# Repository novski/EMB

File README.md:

# EMB

Embedded-Rack is a multi SoC Powersupply with i2c connections.
It can be used to power up to 13 Raspberry Pi's and
 one Microcontroller to monitor Powerconsumption in Rackcase.

## How to

- Get a 19 inch DIN Rack similar to this from [schroff](https://schroff.nvent.com/products/19-subracks).

- Create a Backcover like in the drawing of /powersupply 
accordingly to your powersupply. I use this [MeanWell RSP-200-5](https://www.meanwell.com/productPdf.aspx?i=437)

- Connect a Poweroutlet (with fuse) and solder it to the 
psu and the psu to the backplane with carefully chosen cable 
diameter regarding your psu. 

- Get some Backplane connectors with 24x2.54mm pinn's 
like this from [aliex](https://de.aliexpress.com/wholesale?catId=0&initiative_id=SB_20220409111809&SearchText=pcb+edge+connector).

- Solder some connectors to a daughter-card and push your SoC 
on it.
pi: [mouser](http://ch.mouser.com/Search/ProductDetail.aspx?R=M20-6102045virtualkey57420000virtualkey855-M20-6102045)

- Stick the daughter-board in to the backplane.

## Powermeasureing

The i2c connection between all SoC's can be used as plane 
communication while adding an TI INA219 can be interessting 
to measure power over a board separate. Check the adafruit 
repo's for software and the schematic for parts.

## Impressions

## Disclaimer

All granted for free as in speech, without waranty.
(means that you can use, modify, share, sell if you like. 
But don't try to sue me for mistakes you do yourself.)
Be carefull with Power and re-calculate all wires according 
to your needs.

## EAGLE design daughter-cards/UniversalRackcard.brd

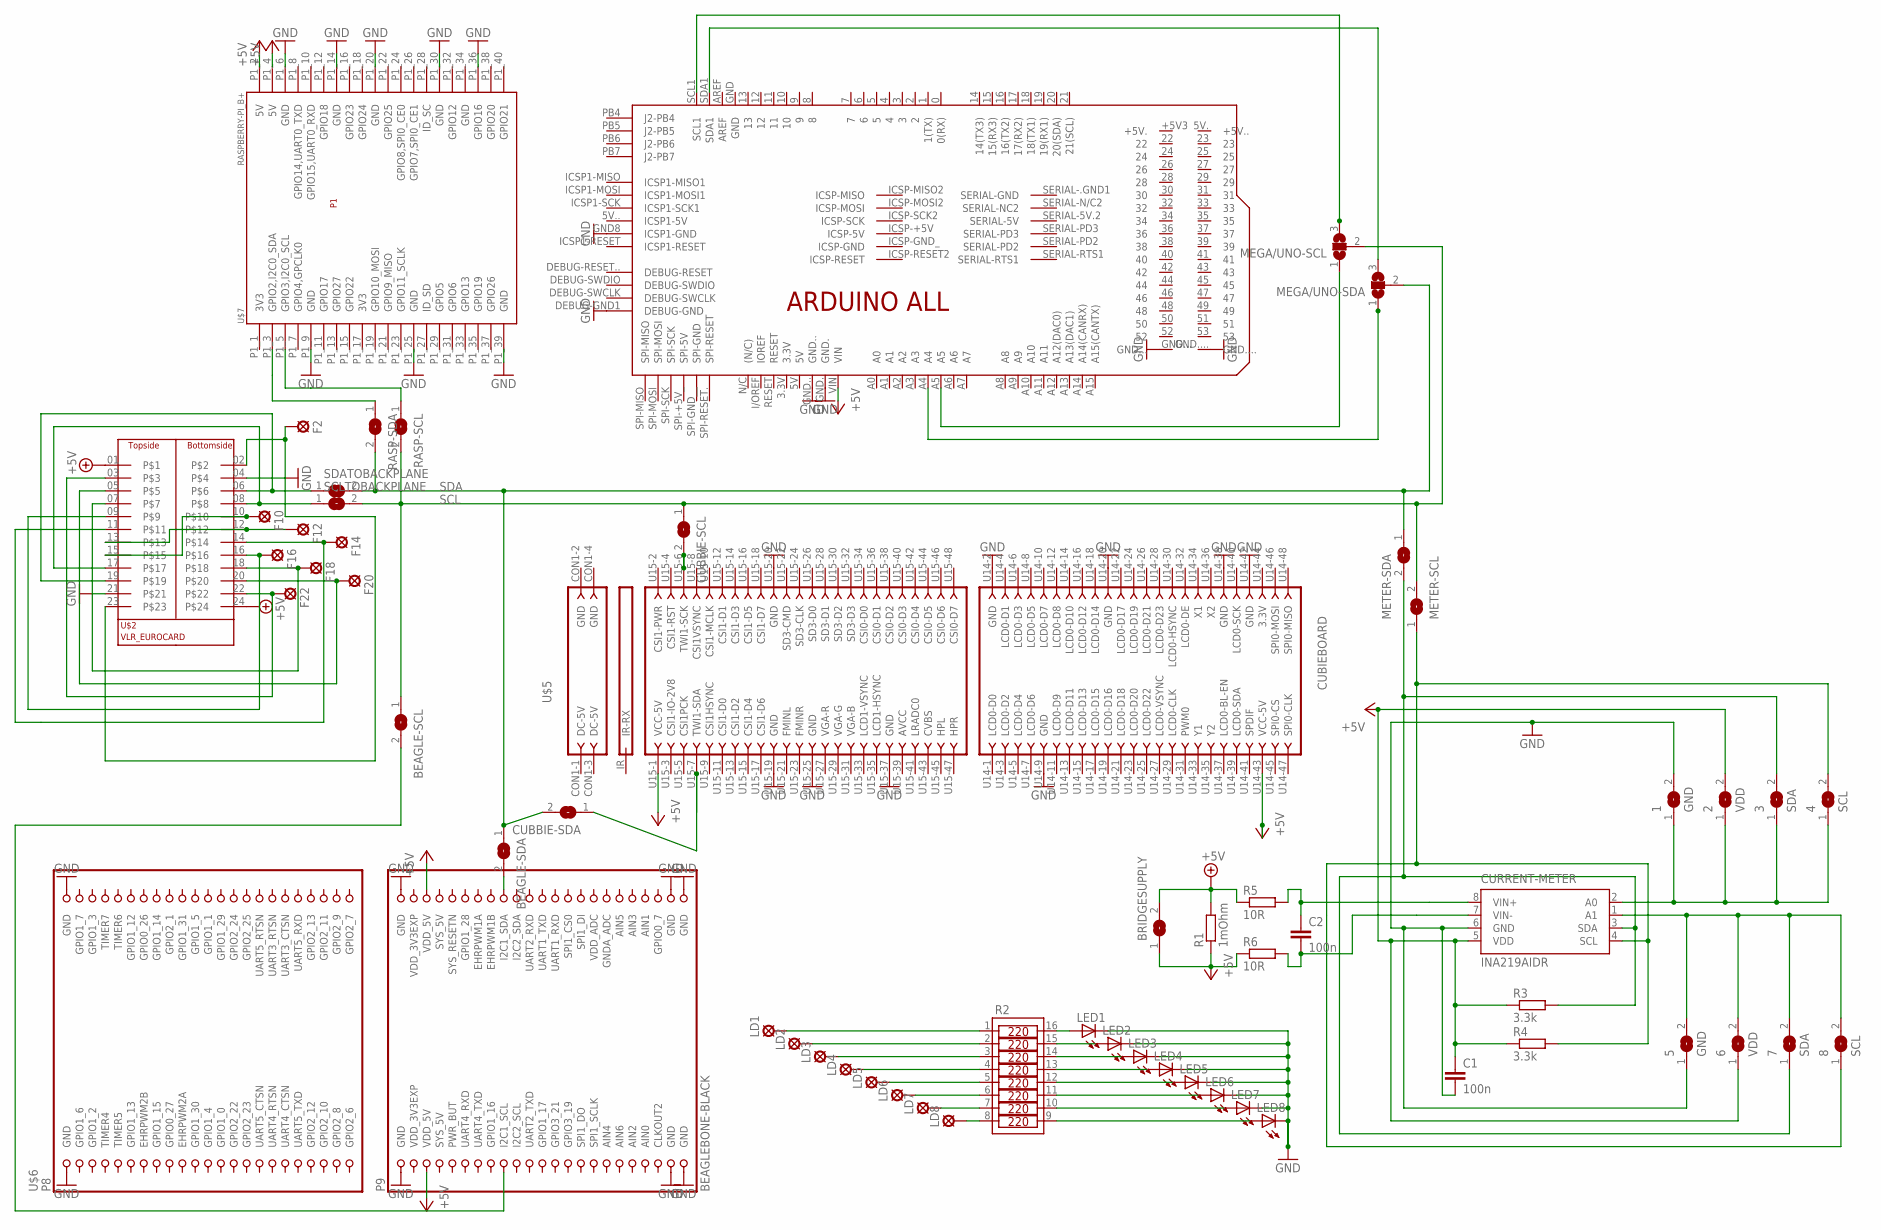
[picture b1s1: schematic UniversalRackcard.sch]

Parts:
1, 5: GND; SJ
2, 6: VDD; SJ
3, 7: SDA; SJ
4, 8: SCL; SJ
BEAGLE-SCL: SJ
BEAGLE-SDA: SJ
BRIDGESUPPLY: SJW
C1, C2: 100n; C025-024X044
CUBBIE-SCL: SJ
CUBBIE-SDA: SJ
CURRENT-METER: INA219AIDR; SO-08
F2, F10, F12, F14, F16, F18, F20, F22: SE13
LD1, LD2, LD3, LD4, LD5, LD6, LD7, LD8: SE13
LED1, LED2, LED3, LED4, LED5, LED6, LED7, LED8: LED3MM
MEGA/UNO-SCL: SJ2W; SJ_2
MEGA/UNO-SDA: SJ2W; SJ_2
METER-SCL: SJ
METER-SDA: SJ
R1: 1mOhm; R2512
R2: 4816P-1SOIC16W; SOIC16W
R3, R4: 3.3k; 0207/7
R5, R6: 10R; 0207/7
RASP-SCL: SJ
RASP-SDA: SJ
SCLTOBACKPLANE: SJ
SDATOBACKPLANE: SJ
U$2: VLR_EUROCARD
U$4: ARDUINO_ALL; ALL
U$5: CUBIEBOARD
U$6: BEAGLEBONE-BLACK; BEAGLEBONE
U$7: RASPBERRY-PI_B+

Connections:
+5V: 2.2, 6.1, BRIDGESUPPLY.1, C1.1, CURRENT-METER.5 (VDD), R1.1, R3.1, R4.1, R6.1, U$4.VIN, U$5.U14-43 (VCC-5V), U$5.U15-1 (VCC-5V), U$6.51 (VDD_5V), U$6.52 (VDD_5V), U$7.P1_2 (5V), U$7.P1_4 (5V)
A0: 1.1, 2.1, 3.1, 4.1, CURRENT-METER.2 (A0)
A1: 5.2, 6.2, 7.2, 8.2, CURRENT-METER.1 (A1)
AIN0: U$6.85 (AIN0)
GND: 1.2, 5.1, C1.2, CURRENT-METER.6 (GND), LED1.K (C), LED2.K (C), LED3.K (C), LED4.K (C), LED5.K (C), LED6.K (C), LED7.K (C), LED8.K (C), U$2.04, U$2.21, U$4.DEBUG-GND1 (DEBUG-GND), U$4.GND8 (ICSP1-GND), U$4.GND., U$4.GND.., U$5.U14-2 (GND), U$5.U14-9 (GND), U$5.U14-20 (GND), U$5.U14-38 (GND), U$5.U14-42 (GND), U$5.U15-19 (GND), U$5.U15-20 (GND), U$5.U15-25 (GND), U$5.U15-37 (GND), U$6.47 (GND), U$6.48 (GND), U$6.89 (GND), U$6.90 (GND), U$6.91 (GND), U$6.92 (GND), U$6.P8-1 (GND), U$6.P8-2 (GND), U$7.P1_6 (GND), U$7.P1_9 (GND), U$7.P1_14 (GND), U$7.P1_20 (GND), U$7.P1_25 (GND), U$7.P1_30 (GND), U$7.P1_36 (GPIO16), U$7.P1_39 (GND)
unnamed: MEGA/UNO-SDA.1, U$4.A4
unnamed: MEGA/UNO-SCL.1, U$4.A5
unnamed: MEGA/UNO-SCL.3, U$4.SCL1
unnamed: MEGA/UNO-SDA.3, U$4.SDA1
unnamed: 3.2, 7.1, CURRENT-METER.3 (SDA), METER-SDA.2, R3.2
unnamed: 4.2, 8.1, CURRENT-METER.4 (SCL), METER-SCL.1, R4.2
unnamed: LD1.MP, R2.1
unnamed: LD2.MP, R2.2
unnamed: LD3.MP, R2.3
unnamed: SDATOBACKPLANE.1, U$2.06, U$2.19
unnamed: SCLTOBACKPLANE.1, U$2.08, U$2.17
unnamed: LD4.MP, R2.4
unnamed: LD5.MP, R2.5
unnamed: LD6.MP, R2.6
unnamed: LD7.MP, R2.7
unnamed: LD8.MP, R2.8
unnamed: LED1.A, R2.16
unnamed: LED2.A, R2.15
unnamed: LED3.A, R2.14
unnamed: LED4.A, R2.13
unnamed: LED6.A, R2.11
unnamed: LED5.A, R2.12
unnamed: LED7.A, R2.10
unnamed: LED8.A, R2.9
unnamed: CUBBIE-SDA.1, U$5.U15-7 (TWI1-SDA)
unnamed: BEAGLE-SDA.2, U$6.64 (I2C1_SDA)
unnamed: BEAGLE-SCL.2, U$6.63 (I2C1_SCL)
unnamed: CUBBIE-SCL.2, U$5.U15-6 (TWI1-SCK)
unnamed: RASP-SCL.1, U$7.P1_5 (GPIO3,I2C0_SCL)
unnamed: RASP-SDA.1, U$7.P1_3 (GPIO2,I2C0_SDA)
unnamed: F2.MP, U$2.02, U$2.23
unnamed: F10.MP, U$2.10, U$2.15
unnamed: F12.MP, U$2.12, U$2.13
unnamed: F14.MP, U$2.11, U$2.14
unnamed: F16.MP, U$2.09, U$2.16
unnamed: F18.MP, U$2.07, U$2.18
unnamed: F20.MP, U$2.05, U$2.20
unnamed: F22.MP, U$2.03, U$2.22
PRIM+5V: BRIDGESUPPLY.2, R1.2, R5.1, U$2.01, U$2.24
SCL: BEAGLE-SCL.1, CUBBIE-SCL.1, MEGA/UNO-SCL.2, METER-SCL.2, RASP-SCL.2, SCLTOBACKPLANE.2
SDA: BEAGLE-SDA.1, CUBBIE-SDA.2, MEGA/UNO-SDA.2, METER-SDA.1, RASP-SDA.2, SDATOBACKPLANE.2
SYS_5V: U$6.53 (SYS_5V)
VDD_3V3EXP: U$6.49 (VDD_3V3EXP), U$6.50 (VDD_3V3EXP)
VIN+: C2.1, CURRENT-METER.8 (VIN+), R5.2
VIN-: C2.2, CURRENT-METER.7 (VIN-), R6.2

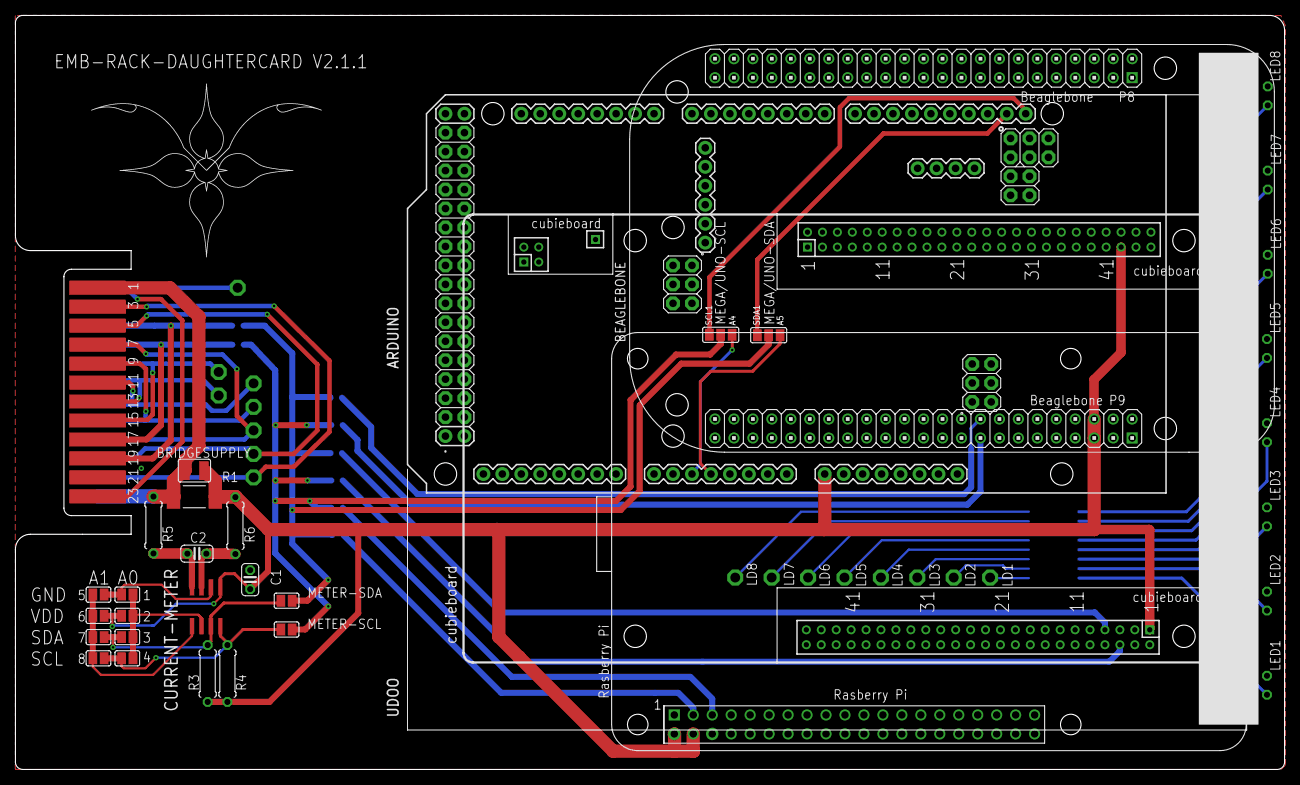
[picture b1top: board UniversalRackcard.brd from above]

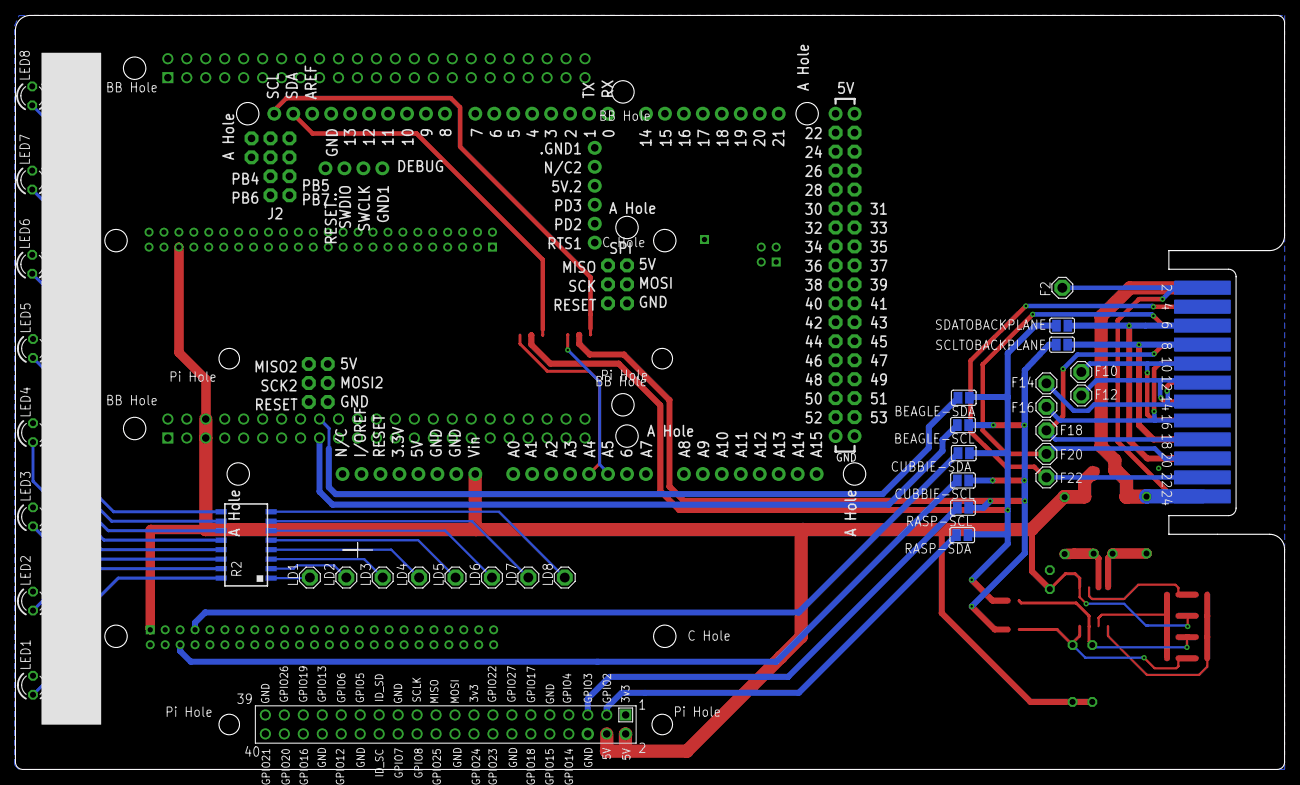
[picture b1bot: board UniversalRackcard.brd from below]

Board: 2 copper layers, 170.0 x 101.0 mm, 61 parts (36 on the bottom side), 48 nets.

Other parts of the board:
U$3, U$8: VLRLAB

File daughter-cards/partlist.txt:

Partlist

Exported from UniversalRackcard.sch at 09.04.22 21:35

EAGLE Version 7.7.0 Copyright (c) 1988-2016 CadSoft

Assembly variant: 

Part           Value            Device           Package         Library               Sheet

1              GND              SJ               SJ              jumper                1
2              VDD              SJ               SJ              jumper                1
3              SDA              SJ               SJ              jumper                1
4              SCL              SJ               SJ              jumper                1
5              GND              SJ               SJ              jumper                1
6              VDD              SJ               SJ              jumper                1
7              SDA              SJ               SJ              jumper                1
8              SCL              SJ               SJ              jumper                1
BEAGLE-SCL                      SJ               SJ              jumper                1
BEAGLE-SDA                      SJ               SJ              jumper                1
BRIDGESUPPLY                    SJW              SJW             jumper                1
C1             100n             C-EU025-024X044  C025-024X044    rcl                   1
C2             100n             C-EU025-024X044  C025-024X044    rcl                   1
CUBBIE-SCL                      SJ               SJ              jumper                1
CUBBIE-SDA                      SJ               SJ              jumper                1
CURRENT-METER  INA219AIDR       INA219AIDR       SO-08           texas                 1
F2             SE13             SE13             SE13            solpad                1
F10            SE13             SE13             SE13            solpad                1
F12            SE13             SE13             SE13            solpad                1
F14            SE13             SE13             SE13            solpad                1
F16            SE13             SE13             SE13            solpad                1
F18            SE13             SE13             SE13            solpad                1
F20            SE13             SE13             SE13            solpad                1
F22            SE13             SE13             SE13            solpad                1
LD1            SE13             SE13             SE13            solpad                1
LD2            SE13             SE13             SE13            solpad                1
LD3            SE13             SE13             SE13            solpad                1
LD4            SE13             SE13             SE13            solpad                1
LD5            SE13             SE13             SE13            solpad                1
LD6            SE13             SE13             SE13            solpad                1
LD7            SE13             SE13             SE13            solpad                1
LD8            SE13             SE13             SE13            solpad                1
LED1                            LED3MM           LED3MM          led                   1
LED2                            LED3MM           LED3MM          led                   1
LED3                            LED3MM           LED3MM          led                   1
LED4                            LED3MM           LED3MM          led                   1
LED5                            LED3MM           LED3MM          led                   1
LED6                            LED3MM           LED3MM          led                   1
LED7                            LED3MM           LED3MM          led                   1
LED8                            LED3MM           LED3MM          led                   1
MEGA/UNO-SCL                    SJ2W             SJ_2            jumper                1
MEGA/UNO-SDA                    SJ2W             SJ_2            jumper                1
METER-SCL                       SJ               SJ              jumper                1
METER-SDA                       SJ               SJ              jumper                1
R1             1mOhm            R-EU_R2512       R2512           resistor              1
R2                              4816P-1SOIC16W   SOIC16W         Bourns Resistor Array 1
R3             3.3k             R-EU_0207/7      0207/7          rcl                   1
R4             3.3k             R-EU_0207/7      0207/7          rcl                   1
R5             10R              R-EU_0207/7      0207/7          rcl                   1
R6             10R              R-EU_0207/7      0207/7          rcl                   1
RASP-SCL                        SJ               SJ              jumper                1
RASP-SDA                        SJ               SJ              jumper                1
SCLTOBACKPLANE                  SJ               SJ              jumper                1
SDATOBACKPLANE                  SJ               SJ              jumper                1
U$2            VLR_EUROCARD     VLR_EUROCARD     VLR_EUROCARD    Frames_VLR            1
U$4            ARDUINO_ALL      ARDUINO_ALL      ALL             Arduino               1
U$5            CUBIEBOARD       CUBIEBOARD       CUBIEBOARD      Cubie                 1
U$6            BEAGLEBONE-BLACK BEAGLEBONE-BLACK BEAGLEBONE      beaglebone            1
U$7            RASPBERRY-PI_B+  RASPBERRY-PI_B+  RASPBERRY-PI_B+ RaspberryPi           1

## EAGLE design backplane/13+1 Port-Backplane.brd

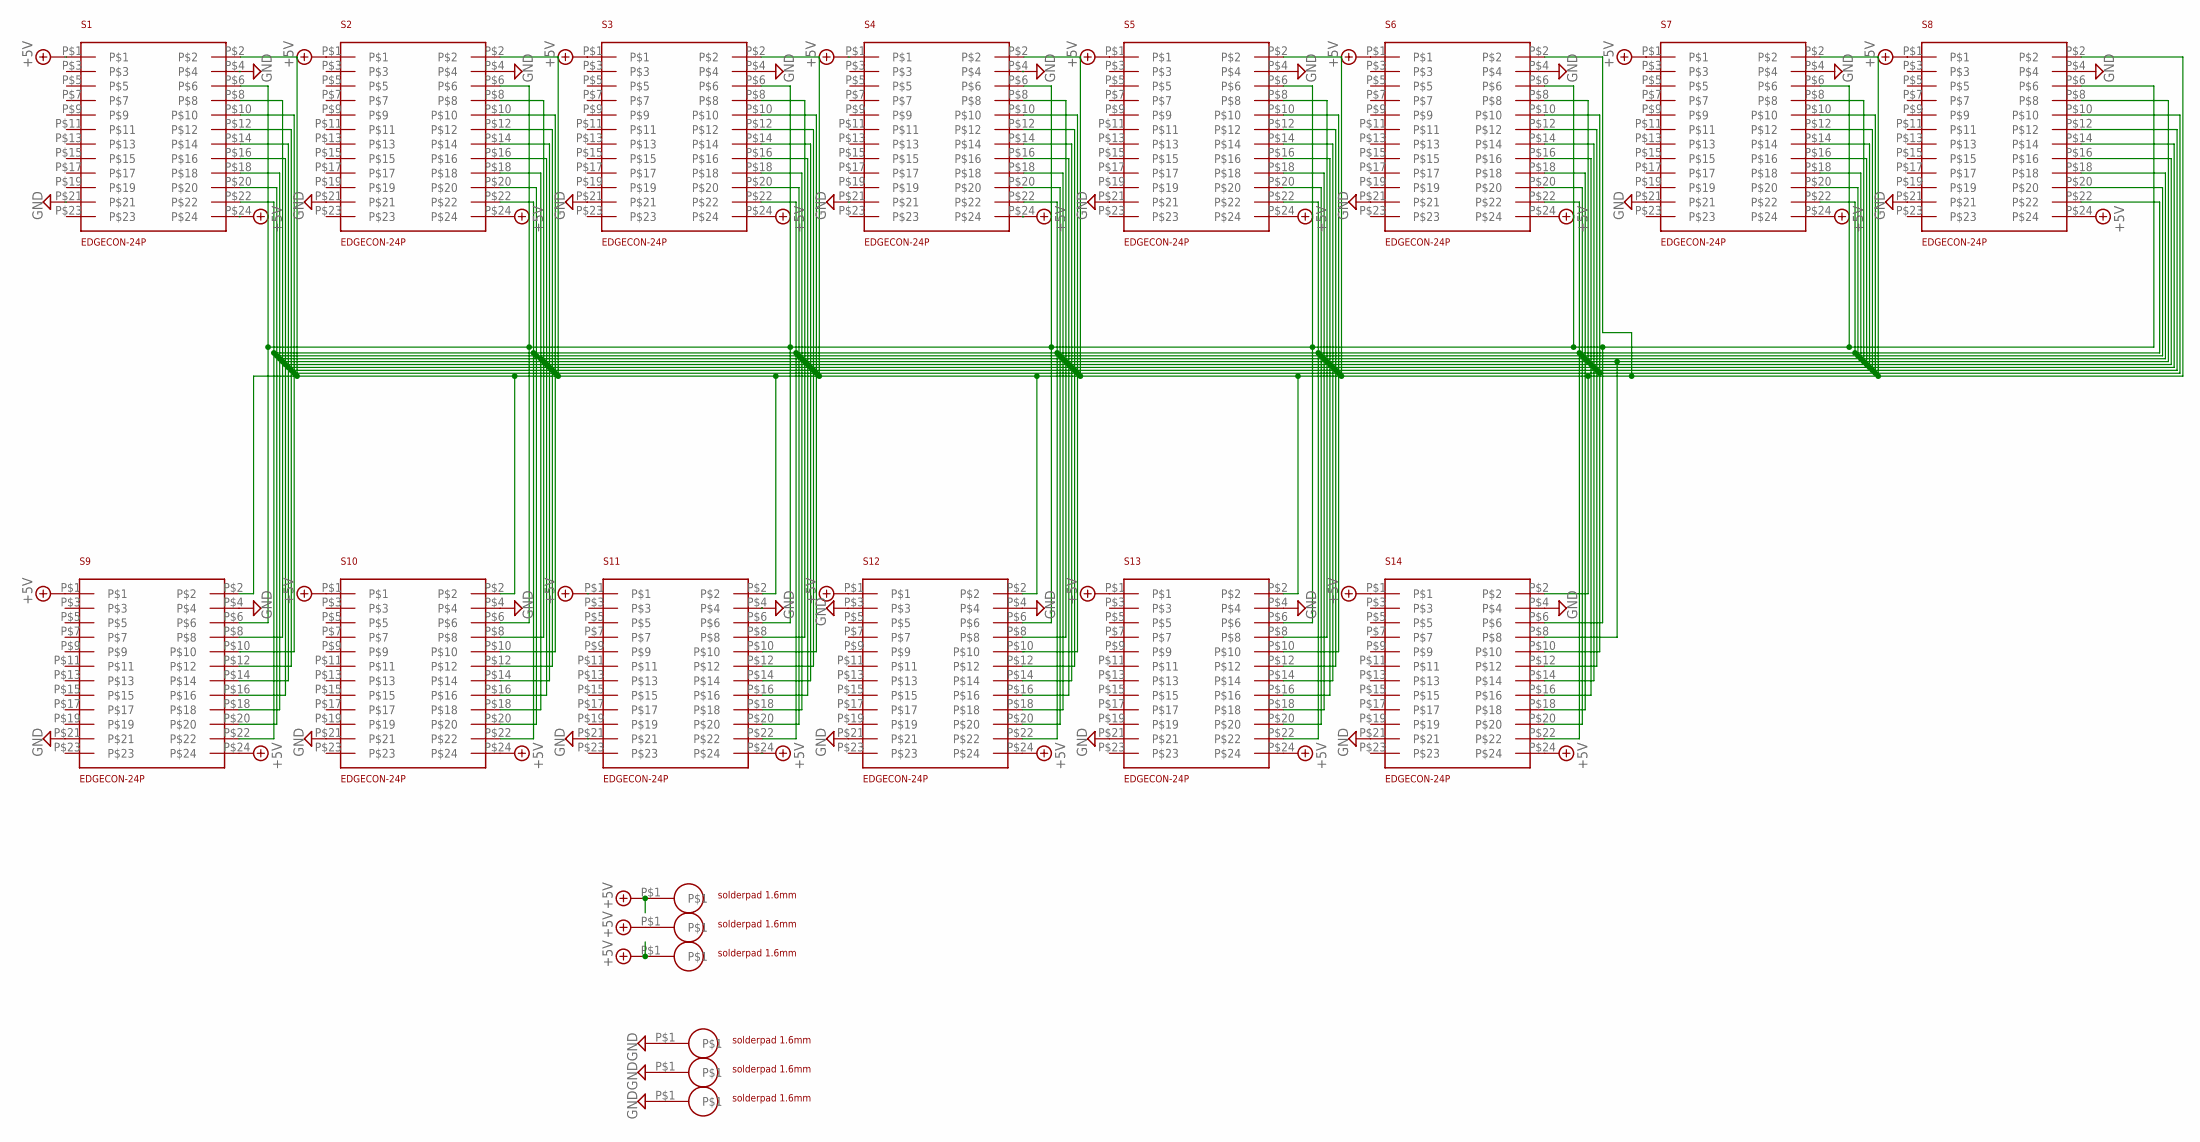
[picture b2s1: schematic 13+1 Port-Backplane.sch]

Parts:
S1, S2, S3, S4, S5, S6, S7, S8, S9, S10, S11, S12, S13, S14: EDGECON-24P; LEDSEE-BOARDCONN24PIN
U$6, U$7, U$8, U$9, U$10, U$11: SOLPAD-1,6MM; SOLDERPAD1.5MM

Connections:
+5V: S1.P$1, S1.P$24, S2.P$1, S2.P$24, S3.P$1, S3.P$24, S4.P$1, S4.P$24, S5.P$1, S5.P$24, S6.P$1, S6.P$24, S7.P$1, S7.P$24, S8.P$1, S8.P$24, S9.P$1, S9.P$24, S10.P$1, S10.P$24, S11.P$1, S11.P$24, S12.P$1, S12.P$24, S13.P$1, S13.P$24, S14.P$1, S14.P$24, U$6.P$1, U$7.P$1, U$9.P$1
GND: S1.P$4, S1.P$21, S2.P$4, S2.P$21, S3.P$4, S3.P$21, S4.P$4, S4.P$21, S5.P$4, S5.P$21, S6.P$4, S6.P$21, S7.P$4, S7.P$21, S8.P$4, S8.P$21, S9.P$4, S9.P$21, S10.P$4, S10.P$21, S11.P$4, S11.P$21, S12.P$3, S12.P$4, S12.P$21, S13.P$4, S13.P$21, S14.P$4, S14.P$21, U$8.P$1, U$10.P$1, U$11.P$1
PIN2: S1.P$2, S2.P$2, S3.P$2, S4.P$2, S5.P$2, S6.P$2, S7.P$2, S8.P$2, S9.P$2, S10.P$2, S11.P$2, S12.P$2, S13.P$2, S14.P$2
PIN6: S1.P$6, S2.P$6, S3.P$6, S4.P$6, S5.P$6, S6.P$6, S7.P$6, S8.P$6, S9.P$6, S10.P$6, S11.P$6, S12.P$6, S13.P$6, S14.P$6
PIN8: S1.P$8, S2.P$8, S3.P$8, S4.P$8, S5.P$8, S6.P$8, S7.P$8, S8.P$8, S9.P$8, S10.P$8, S11.P$8, S12.P$8, S13.P$8, S14.P$8
PIN10: S1.P$10, S2.P$10, S3.P$10, S4.P$10, S5.P$10, S6.P$10, S7.P$10, S8.P$10, S9.P$10, S10.P$10, S11.P$10, S12.P$10, S13.P$10, S14.P$10
PIN12: S1.P$12, S2.P$12, S3.P$12, S4.P$12, S5.P$12, S6.P$12, S7.P$12, S8.P$12, S9.P$12, S10.P$12, S11.P$12, S12.P$12, S13.P$12, S14.P$12
PIN14: S1.P$14, S2.P$14, S3.P$14, S4.P$14, S5.P$14, S6.P$14, S7.P$14, S8.P$14, S9.P$14, S10.P$14, S11.P$14, S12.P$14, S13.P$14, S14.P$14
PIN16: S1.P$16, S2.P$16, S3.P$16, S4.P$16, S5.P$16, S6.P$16, S7.P$16, S8.P$16, S9.P$16, S10.P$16, S11.P$16, S12.P$16, S13.P$16, S14.P$16
PIN18: S1.P$18, S2.P$18, S3.P$18, S4.P$18, S5.P$18, S6.P$18, S7.P$18, S8.P$18, S9.P$18, S10.P$18, S11.P$18, S12.P$18, S13.P$18, S14.P$18
PIN20: S1.P$20, S2.P$20, S3.P$20, S4.P$20, S5.P$20, S6.P$20, S7.P$20, S8.P$20, S9.P$20, S10.P$20, S11.P$20, S12.P$20, S13.P$20, S14.P$20
PIN22: S1.P$22, S2.P$22, S3.P$22, S4.P$22, S5.P$22, S6.P$22, S7.P$22, S8.P$22, S9.P$22, S10.P$22, S11.P$22, S12.P$22, S13.P$22, S14.P$22

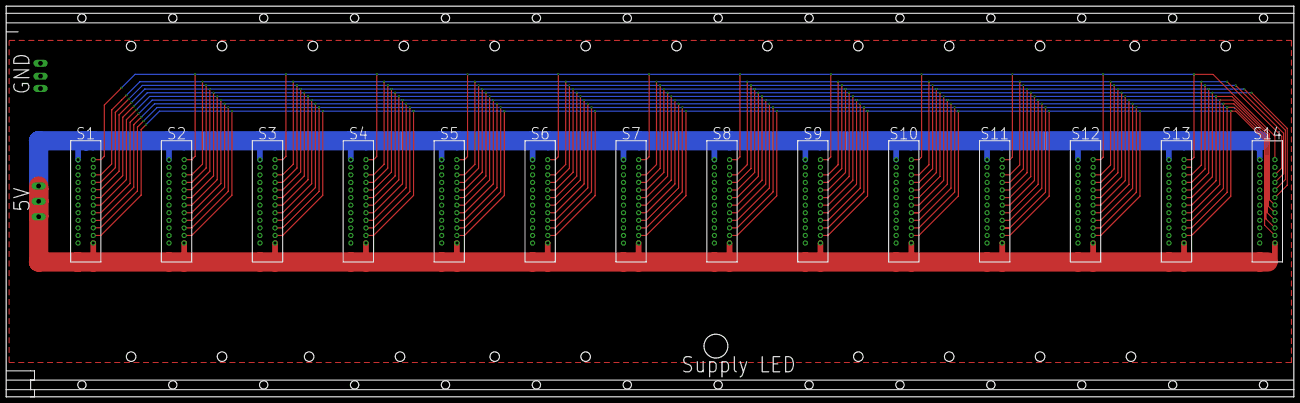
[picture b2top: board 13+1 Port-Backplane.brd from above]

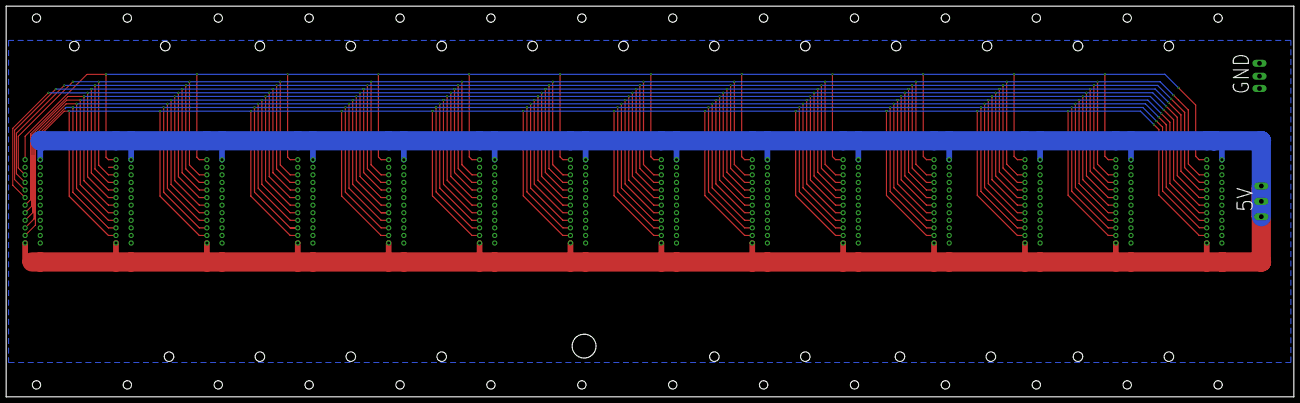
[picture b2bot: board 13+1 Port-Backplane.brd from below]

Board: 2 copper layers, 431.8 x 131.0 mm, 25 parts (2 on the bottom side), 12 nets.

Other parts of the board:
U$2: BAUGRUPPENTRAEGERBACKPLANEFULL@1
U$3, U$4: VLRLAB
U$5, U$12: BACKPLANE

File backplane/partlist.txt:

Partlist

Exported from 13+1 Port-Backplane.sch at 09.04.22 21:37

EAGLE Version 7.7.0 Copyright (c) 1988-2016 CadSoft

Assembly variant: 

Part     Value          Device       Package               Library    Sheet

S1       EDGECON-24P    EDGECON-24P  LEDSEE-BOARDCONN24PIN Ledsee     1
S2       EDGECON-24P    EDGECON-24P  LEDSEE-BOARDCONN24PIN Ledsee     1
S3       EDGECON-24P    EDGECON-24P  LEDSEE-BOARDCONN24PIN Ledsee     1
S4       EDGECON-24P    EDGECON-24P  LEDSEE-BOARDCONN24PIN Ledsee     1
S5       EDGECON-24P    EDGECON-24P  LEDSEE-BOARDCONN24PIN Ledsee     1
S6       EDGECON-24P    EDGECON-24P  LEDSEE-BOARDCONN24PIN Ledsee     1
S7       EDGECON-24P    EDGECON-24P  LEDSEE-BOARDCONN24PIN Ledsee     1
S8       EDGECON-24P    EDGECON-24P  LEDSEE-BOARDCONN24PIN Ledsee     1
S9       EDGECON-24P    EDGECON-24P  LEDSEE-BOARDCONN24PIN Ledsee     1
S10      EDGECON-24P    EDGECON-24P  LEDSEE-BOARDCONN24PIN Ledsee     1
S11      EDGECON-24P    EDGECON-24P  LEDSEE-BOARDCONN24PIN Ledsee     1
S12      EDGECON-24P    EDGECON-24P  LEDSEE-BOARDCONN24PIN Ledsee     1
S13      EDGECON-24P    EDGECON-24P  LEDSEE-BOARDCONN24PIN Ledsee     1
S14      EDGECON-24P    EDGECON-24P  LEDSEE-BOARDCONN24PIN Ledsee     1
U$6      SOLPAD-1,6MM   SOLPAD-1,6MM SOLDERPAD1.5MM        holes_Ivan 1
U$7      SOLPAD-1,6MM   SOLPAD-1,6MM SOLDERPAD1.5MM        holes_Ivan 1
U$8      SOLPAD-1,6MM   SOLPAD-1,6MM SOLDERPAD1.5MM        holes_Ivan 1
U$9      SOLPAD-1,6MM   SOLPAD-1,6MM SOLDERPAD1.5MM        holes_Ivan 1
U$10     SOLPAD-1,6MM   SOLPAD-1,6MM SOLDERPAD1.5MM        holes_Ivan 1
U$11     SOLPAD-1,6MM   SOLPAD-1,6MM SOLDERPAD1.5MM        holes_Ivan 1

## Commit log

2014-11-07 Added Daughterboard
2022-04-09 add recent information
2022-04-10 clarify the licence
2022-04-10 add impressions to readme
2022-04-10 update readme impressions
